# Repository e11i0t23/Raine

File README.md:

# Raine PCB

PCB for the Raine by AKB, Please note the open source version has a reset button added to underside for compatibility with jlcpcb assembly 

---
##### Please Note these PCBs are provided under the MIT Liscence
---

### How to order
The steps bellow outline how to order this pcb with assembly through the JLCPCB platform  

1) From the releases section download CAMOutputs.zip, BOM_Raine.xlsx, and PNP_Raine_Back.xlsx
2) Load the new order section of Jlcpcb, uploading CamOutputs.zip as gerber file
3) Most settings can be left as defualt, reccomend selecting LeadFree HASL under surface finish,
    (Note only Green or Black soldermask can be used with assembly)
4) Enable PCB assembly, choose wanted quantity, and select assemble bottom side then press next
5) For the Bom upload the file BOM_Raine.xlsx, for CPL upload PNP_Raine_Back.xlsx, then press next
6) Ensure file has loaded and no items show out of stock, then press next followed by add to basket
7) Once PCB has arrived QMK firmware can be flashed

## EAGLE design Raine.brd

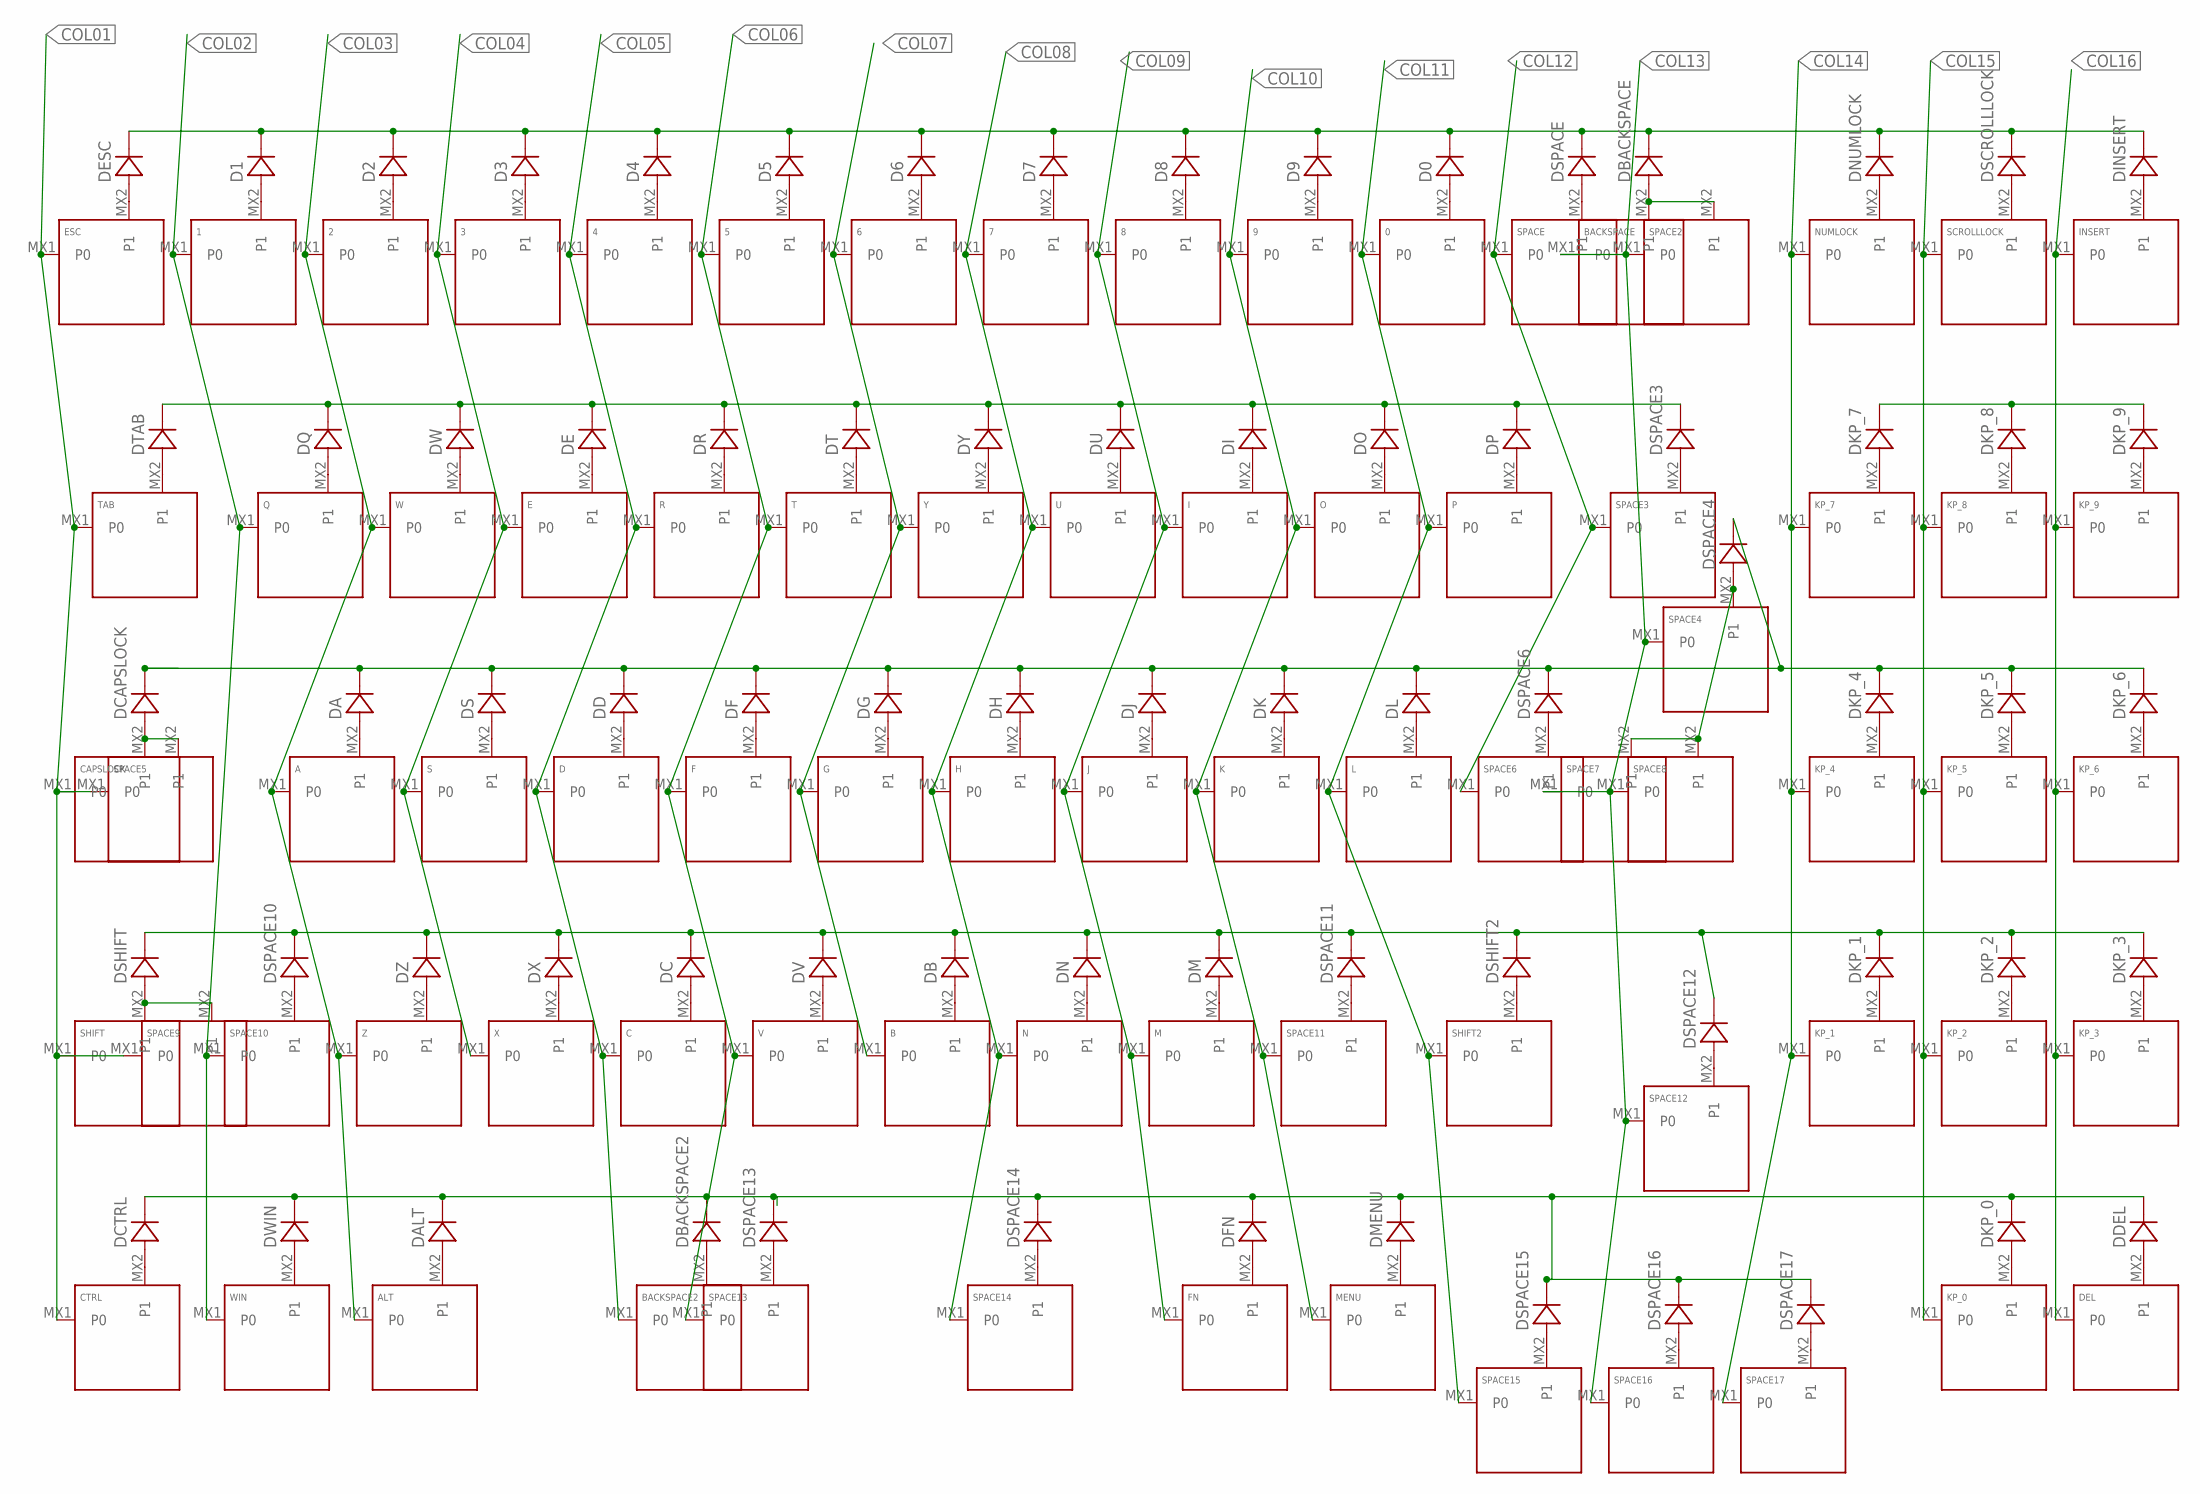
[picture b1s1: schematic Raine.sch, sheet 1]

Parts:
0, 1, 2, 3, 4, 5, 6, 7, 8, 9: KEYSWITCHMX-1U; MX-1U
A: KEYSWITCHMX-1U; MX-1U
ALT: KEYSWITCHMX-1U; MX-1U
B: KEYSWITCHMX-1U; MX-1U
BACKSPACE: KEYSWITCHMX-2U; MX-2U
BACKSPACE2: KEYSWITCHMX-2U-FLIPPED; MX-2U-FLIPPED
C: KEYSWITCHMX-1U; MX-1U
CAPSLOCK: KEYSWITCHMX-1U; MX-1U
CTRL: KEYSWITCHMX-1U; MX-1U
D: KEYSWITCHMX-1U; MX-1U
D0, D1, D2, D3, D4, D5, D6, D7, D8, D9: D_SOD123-SOD-123; SOD-123
DA: D_SOD123-SOD-123; SOD-123
DALT: D_SOD123-SOD-123; SOD-123
DB: D_SOD123-SOD-123; SOD-123
DBACKSPACE, DBACKSPACE2: D_SOD123-SOD-123; SOD-123
DC: D_SOD123-SOD-123; SOD-123
DCAPSLOCK: D_SOD123-SOD-123; SOD-123
DCTRL: D_SOD123-SOD-123; SOD-123
DD: D_SOD123-SOD-123; SOD-123
DDEL: D_SOD123-SOD-123; SOD-123
DE: D_SOD123-SOD-123; SOD-123
DEL: KEYSWITCHMX-1U; MX-1U
DESC: D_SOD123-SOD-123; SOD-123
DF: D_SOD123-SOD-123; SOD-123
DFN: D_SOD123-SOD-123; SOD-123
DG: D_SOD123-SOD-123; SOD-123
DH: D_SOD123-SOD-123; SOD-123
DI: D_SOD123-SOD-123; SOD-123
DINSERT: D_SOD123-SOD-123; SOD-123
DJ: D_SOD123-SOD-123; SOD-123
DK: D_SOD123-SOD-123; SOD-123
DKP_0, DKP_1, DKP_2, DKP_3, DKP_4, DKP_5, DKP_6, DKP_7, DKP_8, DKP_9: D_SOD123-SOD-123; SOD-123
DL: D_SOD123-SOD-123; SOD-123
DM: D_SOD123-SOD-123; SOD-123
DMENU: D_SOD123-SOD-123; SOD-123
DN: D_SOD123-SOD-123; SOD-123
DNUMLOCK: D_SOD123-SOD-123; SOD-123
DO: D_SOD123-SOD-123; SOD-123
DP: D_SOD123-SOD-123; SOD-123
DQ: D_SOD123-SOD-123; SOD-123
DR: D_SOD123-SOD-123; SOD-123
DS: D_SOD123-SOD-123; SOD-123
DSCROLLLOCK: D_SOD123-SOD-123; SOD-123
DSHIFT, DSHIFT2: D_SOD123-SOD-123; SOD-123
DSPACE, DSPACE3, DSPACE4, DSPACE6, DSPACE10, DSPACE11, DSPACE12, DSPACE13, DSPACE14, DSPACE15, DSPACE16, DSPACE17: D_SOD123-SOD-123; SOD-123
DT: D_SOD123-SOD-123; SOD-123
DTAB: D_SOD123-SOD-123; SOD-123
DU: D_SOD123-SOD-123; SOD-123
DV: D_SOD123-SOD-123; SOD-123
DW: D_SOD123-SOD-123; SOD-123
DWIN: D_SOD123-SOD-123; SOD-123
DX: D_SOD123-SOD-123; SOD-123
DY: D_SOD123-SOD-123; SOD-123
DZ: D_SOD123-SOD-123; SOD-123
E: KEYSWITCHMX-1U; MX-1U
ESC: KEYSWITCHMX-1U; MX-1U
F: KEYSWITCHMX-1U; MX-1U
FN: KEYSWITCHMX-1U; MX-1U
G: KEYSWITCHMX-1U; MX-1U
H: KEYSWITCHMX-1U; MX-1U
I: KEYSWITCHMX-1U; MX-1U
INSERT: KEYSWITCHMX-1U; MX-1U
J: KEYSWITCHMX-1U; MX-1U
K: KEYSWITCHMX-1U; MX-1U
KP_0, KP_1, KP_2, KP_3, KP_4, KP_5, KP_6, KP_7, KP_8, KP_9: KEYSWITCHMX-1U; MX-1U
L: KEYSWITCHMX-1U; MX-1U
M: KEYSWITCHMX-1U; MX-1U
MENU: KEYSWITCHMX-1U; MX-1U
N: KEYSWITCHMX-1U; MX-1U
NUMLOCK: KEYSWITCHMX-1U; MX-1U
O: KEYSWITCHMX-1U; MX-1U
P: KEYSWITCHMX-1U; MX-1U
Q: KEYSWITCHMX-1U; MX-1U
R: KEYSWITCHMX-1U; MX-1U
S: KEYSWITCHMX-1U; MX-1U
SCROLLLOCK: KEYSWITCHMX-1U; MX-1U
SHIFT, SHIFT2: KEYSWITCHMX-1U; MX-1U
SPACE, SPACE2, SPACE3, SPACE5, SPACE6, SPACE8, SPACE10, SPACE11, SPACE12, SPACE15, SPACE16, SPACE17: KEYSWITCHMX-1U; MX-1U
SPACE4, SPACE14: KEYSWITCHMX-2U-FLIPPED; MX-2U-FLIPPED
SPACE7, SPACE9: KEYSWITCHMX-2U; MX-2U
SPACE13: KEYSWITCHMX-6.25U-FLIPPED; MX-6.25U-FLIPPED
T: KEYSWITCHMX-1U; MX-1U
TAB: KEYSWITCHMX-1U; MX-1U
U: KEYSWITCHMX-1U; MX-1U
V: KEYSWITCHMX-1U; MX-1U
W: KEYSWITCHMX-1U; MX-1U
WIN: KEYSWITCHMX-1U; MX-1U
X: KEYSWITCHMX-1U; MX-1U
Y: KEYSWITCHMX-1U; MX-1U
Z: KEYSWITCHMX-1U; MX-1U

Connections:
COL01: CAPSLOCK.MX1 (P0), CTRL.MX1 (P0), ESC.MX1 (P0), SHIFT.MX1 (P0), SPACE5.MX1 (P0), SPACE9.MX1 (P0), TAB.MX1 (P0); also elsewhere on the board
COL02: 1.MX1 (P0), Q.MX1 (P0), SPACE10.MX1 (P0), WIN.MX1 (P0); also elsewhere on the board
COL03: 2.MX1 (P0), A.MX1 (P0), ALT.MX1 (P0), W.MX1 (P0), Z.MX1 (P0); also elsewhere on the board
COL04: 3.MX1 (P0), E.MX1 (P0), S.MX1 (P0), X.MX1 (P0); also elsewhere on the board
COL05: 4.MX1 (P0), BACKSPACE2.MX1 (P0), C.MX1 (P0), D.MX1 (P0), R.MX1 (P0); also elsewhere on the board
COL06: 5.MX1 (P0), F.MX1 (P0), SPACE13.MX1 (P0), T.MX1 (P0), V.MX1 (P0); also elsewhere on the board
COL07: 6.MX1 (P0), B.MX1 (P0), G.MX1 (P0), Y.MX1 (P0); also elsewhere on the board
COL08: 7.MX1 (P0), H.MX1 (P0), N.MX1 (P0), SPACE14.MX1 (P0), U.MX1 (P0); also elsewhere on the board
COL09: 8.MX1 (P0), FN.MX1 (P0), I.MX1 (P0), J.MX1 (P0), M.MX1 (P0); also elsewhere on the board
COL10: 9.MX1 (P0), K.MX1 (P0), MENU.MX1 (P0), O.MX1 (P0), SPACE11.MX1 (P0); also elsewhere on the board
COL11: 0.MX1 (P0), L.MX1 (P0), P.MX1 (P0), SHIFT2.MX1 (P0), SPACE15.MX1 (P0); also elsewhere on the board
COL12: SPACE.MX1 (P0), SPACE3.MX1 (P0), SPACE6.MX1 (P0); also elsewhere on the board
COL13: BACKSPACE.MX1 (P0), SPACE2.MX1 (P0), SPACE4.MX1 (P0), SPACE7.MX1 (P0), SPACE8.MX1 (P0), SPACE12.MX1 (P0), SPACE16.MX1 (P0); also elsewhere on the board
COL14: KP_1.MX1 (P0), KP_4.MX1 (P0), KP_7.MX1 (P0), NUMLOCK.MX1 (P0), SPACE17.MX1 (P0); also elsewhere on the board
COL15: KP_0.MX1 (P0), KP_2.MX1 (P0), KP_5.MX1 (P0), KP_8.MX1 (P0), SCROLLLOCK.MX1 (P0); also elsewhere on the board
COL16: DEL.MX1 (P0), INSERT.MX1 (P0), KP_3.MX1 (P0), KP_6.MX1 (P0), KP_9.MX1 (P0); also elsewhere on the board
unnamed: DTAB.A, TAB.MX2 (P1)
unnamed: DQ.A, Q.MX2 (P1)
unnamed: DW.A, W.MX2 (P1)
unnamed: DE.A, E.MX2 (P1)
unnamed: DR.A, R.MX2 (P1)
unnamed: DT.A, T.MX2 (P1)
unnamed: DY.A, Y.MX2 (P1)
unnamed: DU.A, U.MX2 (P1)
unnamed: DI.A, I.MX2 (P1)
unnamed: DO.A, O.MX2 (P1)
unnamed: DP.A, P.MX2 (P1)
unnamed: DSPACE3.A, SPACE3.MX2 (P1)
unnamed: DKP_7.A, KP_7.MX2 (P1)
unnamed: DKP_8.A, KP_8.MX2 (P1)
unnamed: DKP_9.A, KP_9.MX2 (P1)
unnamed: DNUMLOCK.A, NUMLOCK.MX2 (P1)
unnamed: CAPSLOCK.MX2 (P1), DCAPSLOCK.A, SPACE5.MX2 (P1)
unnamed: A.MX2 (P1), DA.A
unnamed: DS.A, S.MX2 (P1)
unnamed: D.MX2 (P1), DD.A
unnamed: DF.A, F.MX2 (P1)
unnamed: DG.A, G.MX2 (P1)
unnamed: DH.A, H.MX2 (P1)
unnamed: DJ.A, J.MX2 (P1)
unnamed: DK.A, K.MX2 (P1)
unnamed: DL.A, L.MX2 (P1)
unnamed: DSPACE6.A, SPACE6.MX2 (P1)
unnamed: DSPACE4.A, SPACE4.MX2 (P1), SPACE7.MX2 (P1), SPACE8.MX2 (P1)
unnamed: DSCROLLLOCK.A, SCROLLLOCK.MX2 (P1)
unnamed: DKP_4.A, KP_4.MX2 (P1)
unnamed: DKP_5.A, KP_5.MX2 (P1)
unnamed: DKP_6.A, KP_6.MX2 (P1)
unnamed: DSHIFT.A, SHIFT.MX2 (P1), SPACE9.MX2 (P1)
unnamed: DINSERT.A, INSERT.MX2 (P1)
unnamed: DSPACE10.A, SPACE10.MX2 (P1)
unnamed: DZ.A, Z.MX2 (P1)
unnamed: DX.A, X.MX2 (P1)
unnamed: C.MX2 (P1), DC.A
unnamed: DV.A, V.MX2 (P1)
unnamed: B.MX2 (P1), DB.A
unnamed: DN.A, N.MX2 (P1)
unnamed: DM.A, M.MX2 (P1)
unnamed: DSPACE11.A, SPACE11.MX2 (P1)
unnamed: DSHIFT2.A, SHIFT2.MX2 (P1)
unnamed: DKP_1.A, KP_1.MX2 (P1)
unnamed: DKP_2.A, KP_2.MX2 (P1)
unnamed: DKP_3.A, KP_3.MX2 (P1)
unnamed: DSPACE12.A, SPACE12.MX2 (P1)
unnamed: CTRL.MX2 (P1), DCTRL.A
unnamed: DWIN.A, WIN.MX2 (P1)
unnamed: ALT.MX2 (P1), DALT.A
unnamed: DSPACE13.A, SPACE13.MX2 (P1)
unnamed: BACKSPACE2.MX2 (P1), DBACKSPACE2.A
unnamed: DSPACE14.A, SPACE14.MX2 (P1)
unnamed: DFN.A, FN.MX2 (P1)
unnamed: DMENU.A, MENU.MX2 (P1)
unnamed: DKP_0.A, KP_0.MX2 (P1)
unnamed: DDEL.A, DEL.MX2 (P1)
unnamed: DSPACE15.A, SPACE15.MX2 (P1)
unnamed: DSPACE16.A, SPACE16.MX2 (P1)
unnamed: DSPACE17.A, SPACE17.MX2 (P1)
unnamed: DSPACE.A, SPACE.MX2 (P1)
unnamed: 0.MX2 (P1), D0.A
unnamed: 9.MX2 (P1), D9.A
unnamed: 8.MX2 (P1), D8.A
unnamed: 7.MX2 (P1), D7.A
unnamed: 6.MX2 (P1), D6.A
unnamed: 5.MX2 (P1), D5.A
unnamed: DESC.A, ESC.MX2 (P1)
unnamed: 1.MX2 (P1), D1.A
unnamed: 2.MX2 (P1), D2.A
unnamed: 3.MX2 (P1), D3.A
unnamed: 4.MX2 (P1), D4.A
unnamed: BACKSPACE.MX2 (P1), DBACKSPACE.A, SPACE2.MX2 (P1)
ROW1: D0.C, D1.C, D2.C, D3.C, D4.C, D5.C, D6.C, D7.C, D8.C, D9.C, DBACKSPACE.C, DESC.C, DINSERT.C, DNUMLOCK.C, DSCROLLLOCK.C, DSPACE.C; also elsewhere on the board
ROW2: DE.C, DI.C, DKP_7.C, DKP_8.C, DKP_9.C, DO.C, DP.C, DQ.C, DR.C, DSPACE3.C, DT.C, DTAB.C, DU.C, DW.C, DY.C; also elsewhere on the board
ROW3: DA.C, DCAPSLOCK.C, DD.C, DF.C, DG.C, DH.C, DJ.C, DK.C, DKP_4.C, DKP_5.C, DKP_6.C, DL.C, DS.C, DSPACE4.C, DSPACE6.C; also elsewhere on the board
ROW4: DB.C, DC.C, DKP_1.C, DKP_2.C, DKP_3.C, DM.C, DN.C, DSHIFT.C, DSHIFT2.C, DSPACE10.C, DSPACE11.C, DSPACE12.C, DV.C, DX.C, DZ.C; also elsewhere on the board
ROW5.25: DALT.C, DBACKSPACE2.C, DCTRL.C, DDEL.C, DFN.C, DKP_0.C, DMENU.C, DSPACE13.C, DSPACE14.C, DSPACE15.C, DSPACE16.C, DSPACE17.C, DWIN.C; also elsewhere on the board

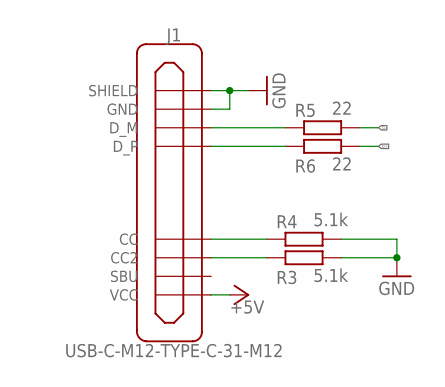
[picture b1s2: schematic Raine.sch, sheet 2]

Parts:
J1: USB-C-M12-TYPE-C-31-M12; TYPE-C-31-M-12
R3, R4: 5.1k; CAPC1608X90
R5, R6: 22; CAPC1608X90

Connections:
+5V: J1.P$2 (VCC), J1.P$11 (VCC); also elsewhere on the board
D+: R6.2; also elsewhere on the board
D-: R5.2; also elsewhere on the board
GND: J1.P$1 (GND), J1.P$12 (GND), J1.P$13 (SHIELD), J1.P$14 (SHIELD), J1.P$15 (SHIELD), J1.P$16 (SHIELD), R3.2, R4.2; also elsewhere on the board
unnamed: J1.P$6 (D_P), J1.P$8 (D_P), R6.1
unnamed: J1.P$5 (D_M), J1.P$7 (D_M), R5.1
unnamed: J1.P$10 (CC2), R3.1
unnamed: J1.P$4 (CC), R4.1

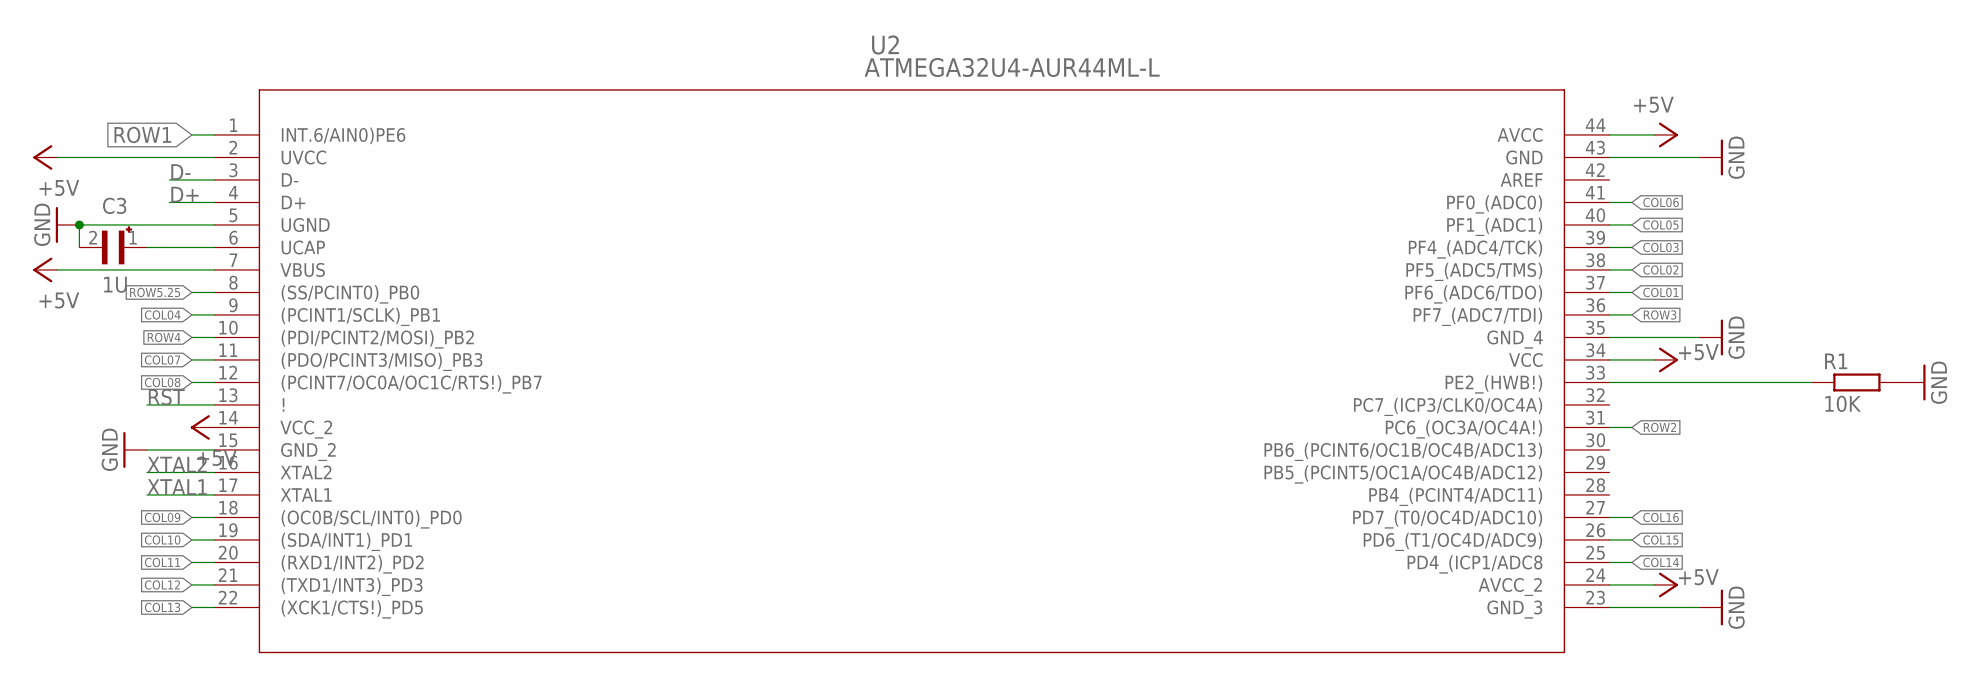
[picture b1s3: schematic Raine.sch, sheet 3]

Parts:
C3: 1U; CAPC1608X90
R1: 10K; CAPC1608X90
U2: ATMEGA32U4-AUR44ML-L; 44ML-L

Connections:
+5V: U2.2 (UVCC), U2.7 (VBUS), U2.14 (VCC_2), U2.24 (AVCC_2), U2.34 (VCC), U2.44 (AVCC); also elsewhere on the board
COL01: U2.37 (PF6_(ADC6/TDO)); also elsewhere on the board
COL02: U2.38 (PF5_(ADC5/TMS)); also elsewhere on the board
COL03: U2.39 (PF4_(ADC4/TCK)); also elsewhere on the board
COL04: U2.9 ((PCINT1/SCLK)_PB1); also elsewhere on the board
COL05: U2.40 (PF1_(ADC1)); also elsewhere on the board
COL06: U2.41 (PF0_(ADC0)); also elsewhere on the board
COL07: U2.11 ((PDO/PCINT3/MISO)_PB3); also elsewhere on the board
COL08: U2.12 ((PCINT7/OC0A/OC1C/RTS!)_PB7); also elsewhere on the board
COL09: U2.18 ((OC0B/SCL/INT0)_PD0); also elsewhere on the board
COL10: U2.19 ((SDA/INT1)_PD1); also elsewhere on the board
COL11: U2.20 ((RXD1/INT2)_PD2); also elsewhere on the board
COL12: U2.21 ((TXD1/INT3)_PD3); also elsewhere on the board
COL13: U2.22 ((XCK1/CTS!)_PD5); also elsewhere on the board
COL14: U2.25 (PD4_(ICP1/ADC8); also elsewhere on the board
COL15: U2.26 (PD6_(T1/OC4D/ADC9)); also elsewhere on the board
COL16: U2.27 (PD7_(T0/OC4D/ADC10)); also elsewhere on the board
D+: U2.4 (D+); also elsewhere on the board
D-: U2.3 (D-); also elsewhere on the board
GND: C3.2, R1.2, U2.5 (UGND), U2.15 (GND_2), U2.23 (GND_3), U2.35 (GND_4), U2.43 (GND); also elsewhere on the board
unnamed: C3.1, U2.6 (UCAP)
unnamed: R1.1, U2.33 (PE2_(HWB!))
ROW1: U2.1 (INT.6/AIN0)PE6); also elsewhere on the board
ROW2: U2.31 (PC6_(OC3A/OC4A!)); also elsewhere on the board
ROW3: U2.36 (PF7_(ADC7/TDI)); also elsewhere on the board
ROW4: U2.10 ((PDI/PCINT2/MOSI)_PB2); also elsewhere on the board
ROW5.25: U2.8 ((SS/PCINT0)_PB0); also elsewhere on the board
RST: U2.13 (!); also elsewhere on the board
XTAL1: U2.17 (XTAL1); also elsewhere on the board
XTAL2: U2.16 (XTAL2); also elsewhere on the board

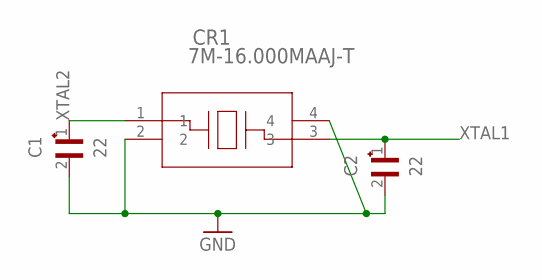
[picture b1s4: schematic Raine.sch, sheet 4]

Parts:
C1, C2: 22; CAPC1608X90
CR1: 7M-16.000MAAJ-T; CRYSTAL_TXC_7M

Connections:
GND: C1.2, C2.2, CR1.2, CR1.4; also elsewhere on the board
XTAL1: C2.1, CR1.3; also elsewhere on the board
XTAL2: C1.1, CR1.1; also elsewhere on the board

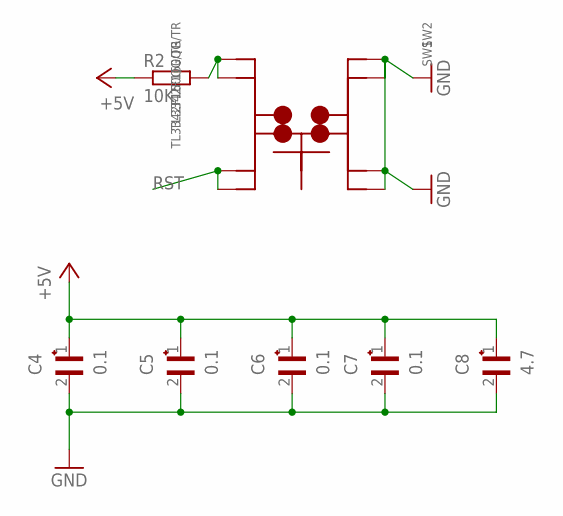
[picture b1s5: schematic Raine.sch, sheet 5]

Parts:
C4, C5, C6, C7: 0.1; CAPC1608X90
C8: 4.7; CAPC1608X90
R2: 10K; CAPC1608X90
SW1, SW2: TL3342F160QG/TR; SW_TL3342F160QG/TR

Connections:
+5V: C4.1, C5.1, C6.1, C7.1, C8.1, R2.1; also elsewhere on the board
GND: C4.2, C5.2, C6.2, C7.2, C8.2, SW1.3, SW1.4, SW2.3, SW2.4; also elsewhere on the board
unnamed: R2.2, SW1.1, SW2.1
RST: SW1.2, SW2.2; also elsewhere on the board

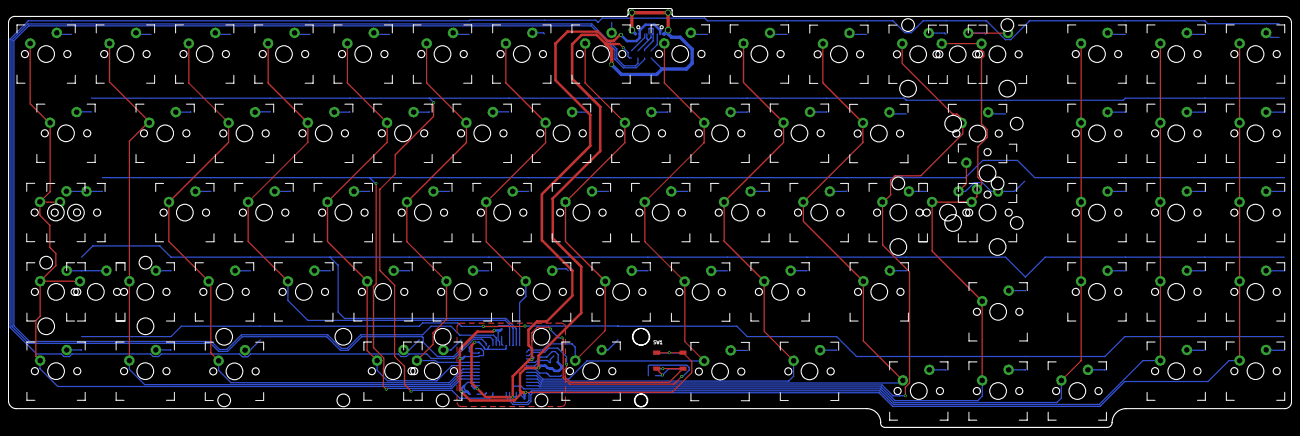
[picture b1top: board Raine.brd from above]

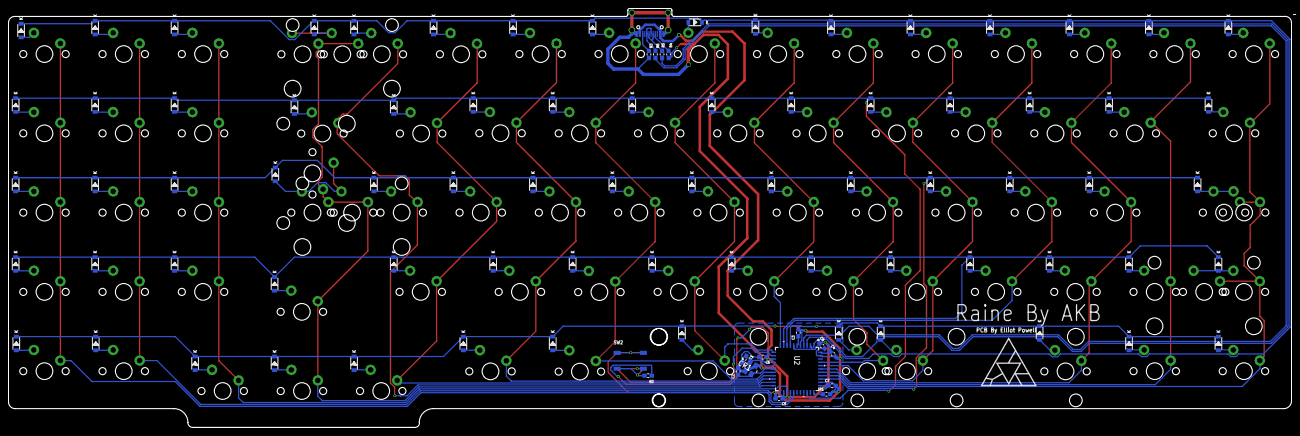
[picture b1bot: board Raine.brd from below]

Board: 2 copper layers, 307.5 x 100.4 mm, 172 parts (91 on the bottom side), 109 nets.

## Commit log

2020-07-24 innit
2022-05-15 minor trace moves
2022-05-26 Add reset switch to bottom of pcb
2022-05-26 Update Production files
2022-05-26 Update for JLCPCB
2022-05-26 fix typo
